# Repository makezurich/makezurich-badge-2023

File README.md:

## #MakeZurich 2023 Badge

## Pinout

## PSU
* Adafruit Feather LiPo circuit

## IO
* LoRa E5
* Shitty Addon
* Cover connectors 
* Grove connectors

## Resources

### CircuitPython
https://github.com/makezurich/badge2023-circuitpython

https://github.com/todbot/circuitpython-tricks

https://www.circuitpython.org

### LoRa E5
https://wiki.seeedstudio.com/Grove_LoRa_E5_New_Version/

https://www.hackster.io/sidikalamini/grove-lora-e5-p2p-communication-using-circuitpython-f970e6

https://files.seeedstudio.com/products/317990687/res/LoRa-E5%20AT%20Command%20Specification_V1.0%20.pdf

#### Version
| title | date | author | id | mainfont | toc | toc-depth |
| --- | --- | --- | --- | --- | --- | --- |
|"Badge"|2022-09-20|Tillo|20220920183855|Cochin|true|2|
|"Badge"|2023-04-24|Fede|?|Cochin|true|2|
|"Badge"|2023-05-12|Fede|?|Cochin|true|2|

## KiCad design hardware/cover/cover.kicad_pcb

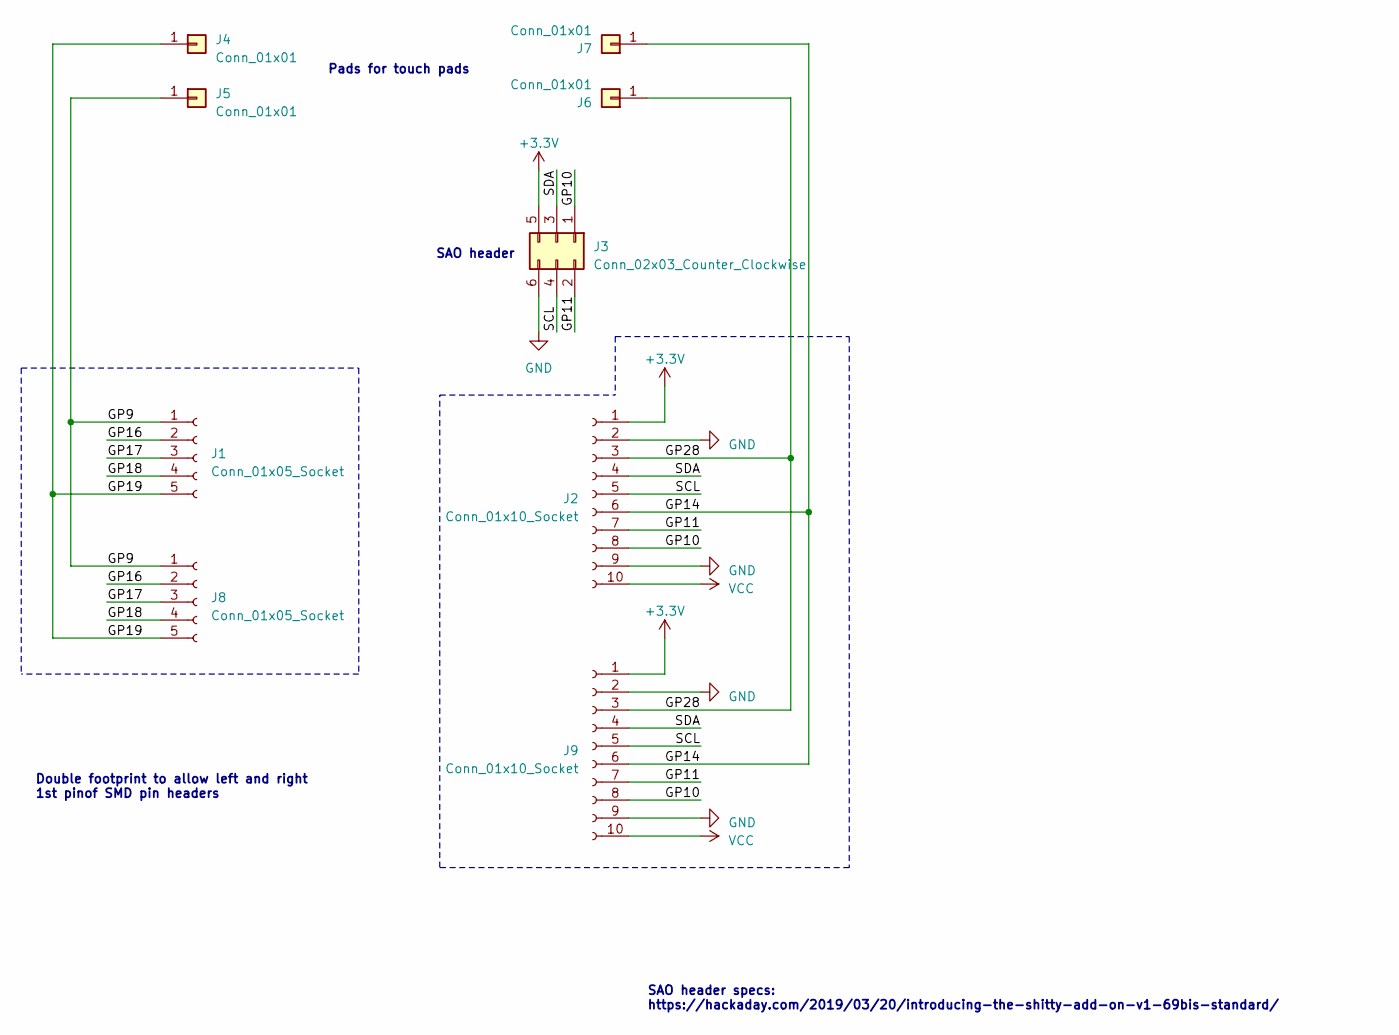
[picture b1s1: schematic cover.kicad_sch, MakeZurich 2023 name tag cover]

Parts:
J1: Conn_01x05_Socket; PinHeader_1x05_P2.54mm_Vertical_SMD_Pin1Right
J2: Conn_01x10_Socket; PinHeader_1x10_P2.54mm_Vertical_SMD_Pin1Left
J3: Conn_02x03_Counter_Clockwise; IDC-Header_2x03_P2.54mm_Vertical
J4, J5, J6, J7: Conn_01x01; SolderWirePad_1x01_SMD_1x2mm
J8: Conn_01x05_Socket; PinHeader_1x05_P2.54mm_Vertical_SMD_Pin1Left
J9: Conn_01x10_Socket; PinHeader_1x10_P2.54mm_Vertical_SMD_Pin1Right

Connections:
+3.3V: J2.1, J3.5, J9.1
/GP9: J1.1, J5.1, J8.1
/GP10: J2.8, J3.1, J9.8
/GP11: J2.7, J3.2, J9.7
/GP14: J2.6, J7.1, J9.6
/GP16: J1.2, J8.2
/GP17: J1.3, J8.3
/GP18: J1.4, J8.4
/GP19: J1.5, J4.1, J8.5
/GP28: J2.3, J6.1, J9.3
/SCL: J2.5, J3.4, J9.5
/SDA: J2.4, J3.3, J9.4
GND: J2.2, J2.9, J3.6, J9.2, J9.9
VCC: J2.10, J9.10

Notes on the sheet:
Double footprint to allow left and right 1st pinof SMD pin headers
SAO header
SAO header specs: https://hackaday.com/2019/03/20/introducing-the-shitty-add-on-v1-69bis-standard/
Pads for touch pads

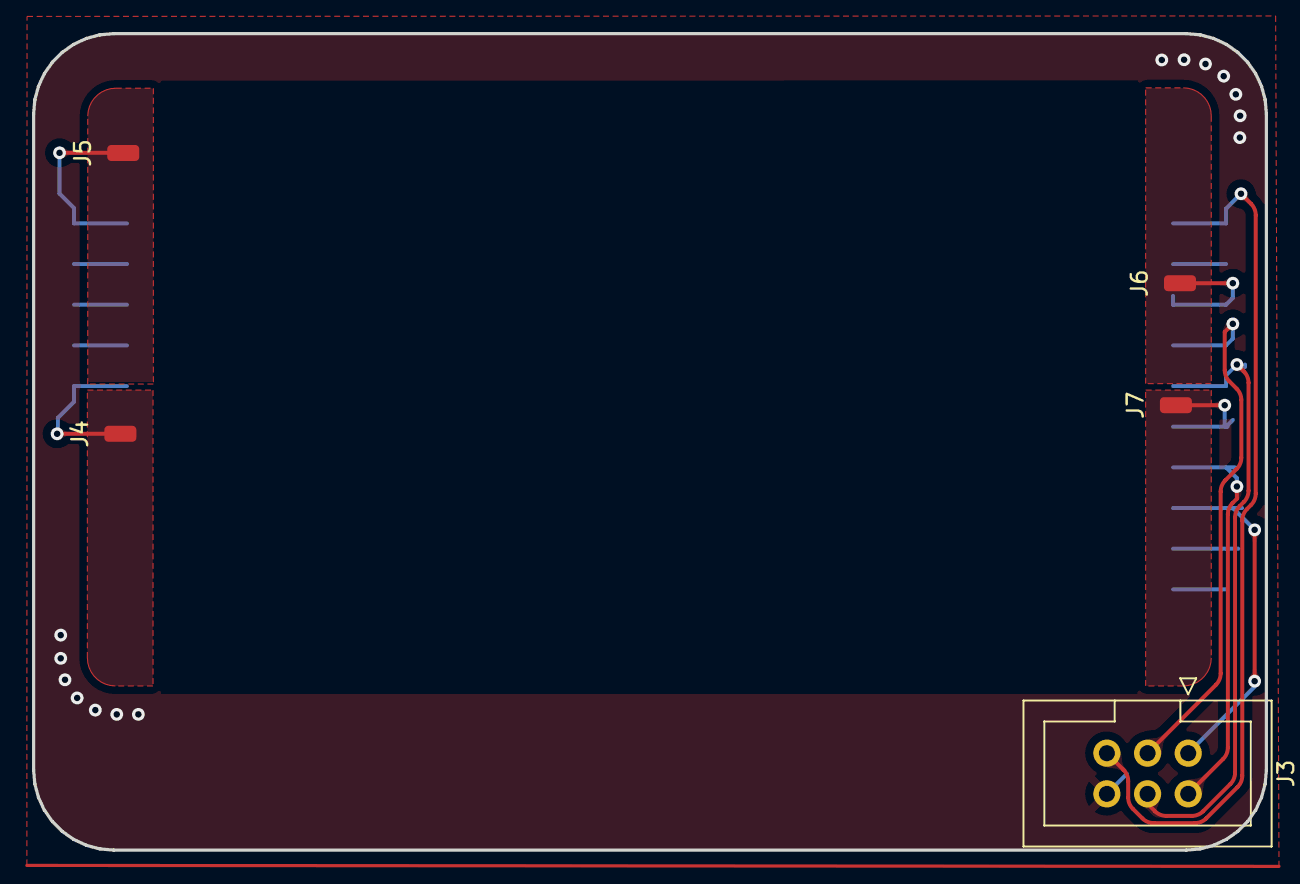
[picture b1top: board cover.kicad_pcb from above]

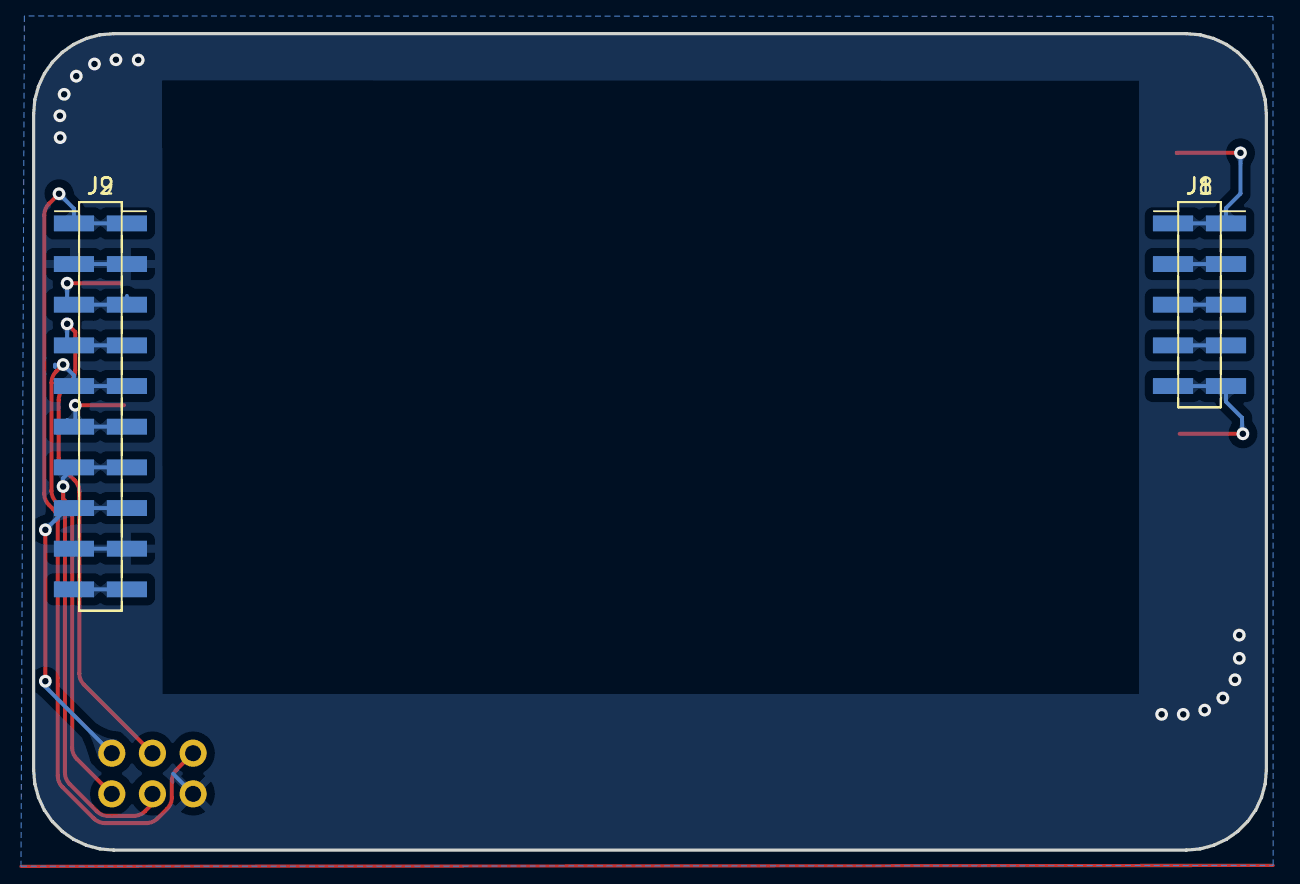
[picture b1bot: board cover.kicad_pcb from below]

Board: 2 copper layers, 77.0 x 51.0 mm, 9 parts (4 on the bottom side), 14 nets.

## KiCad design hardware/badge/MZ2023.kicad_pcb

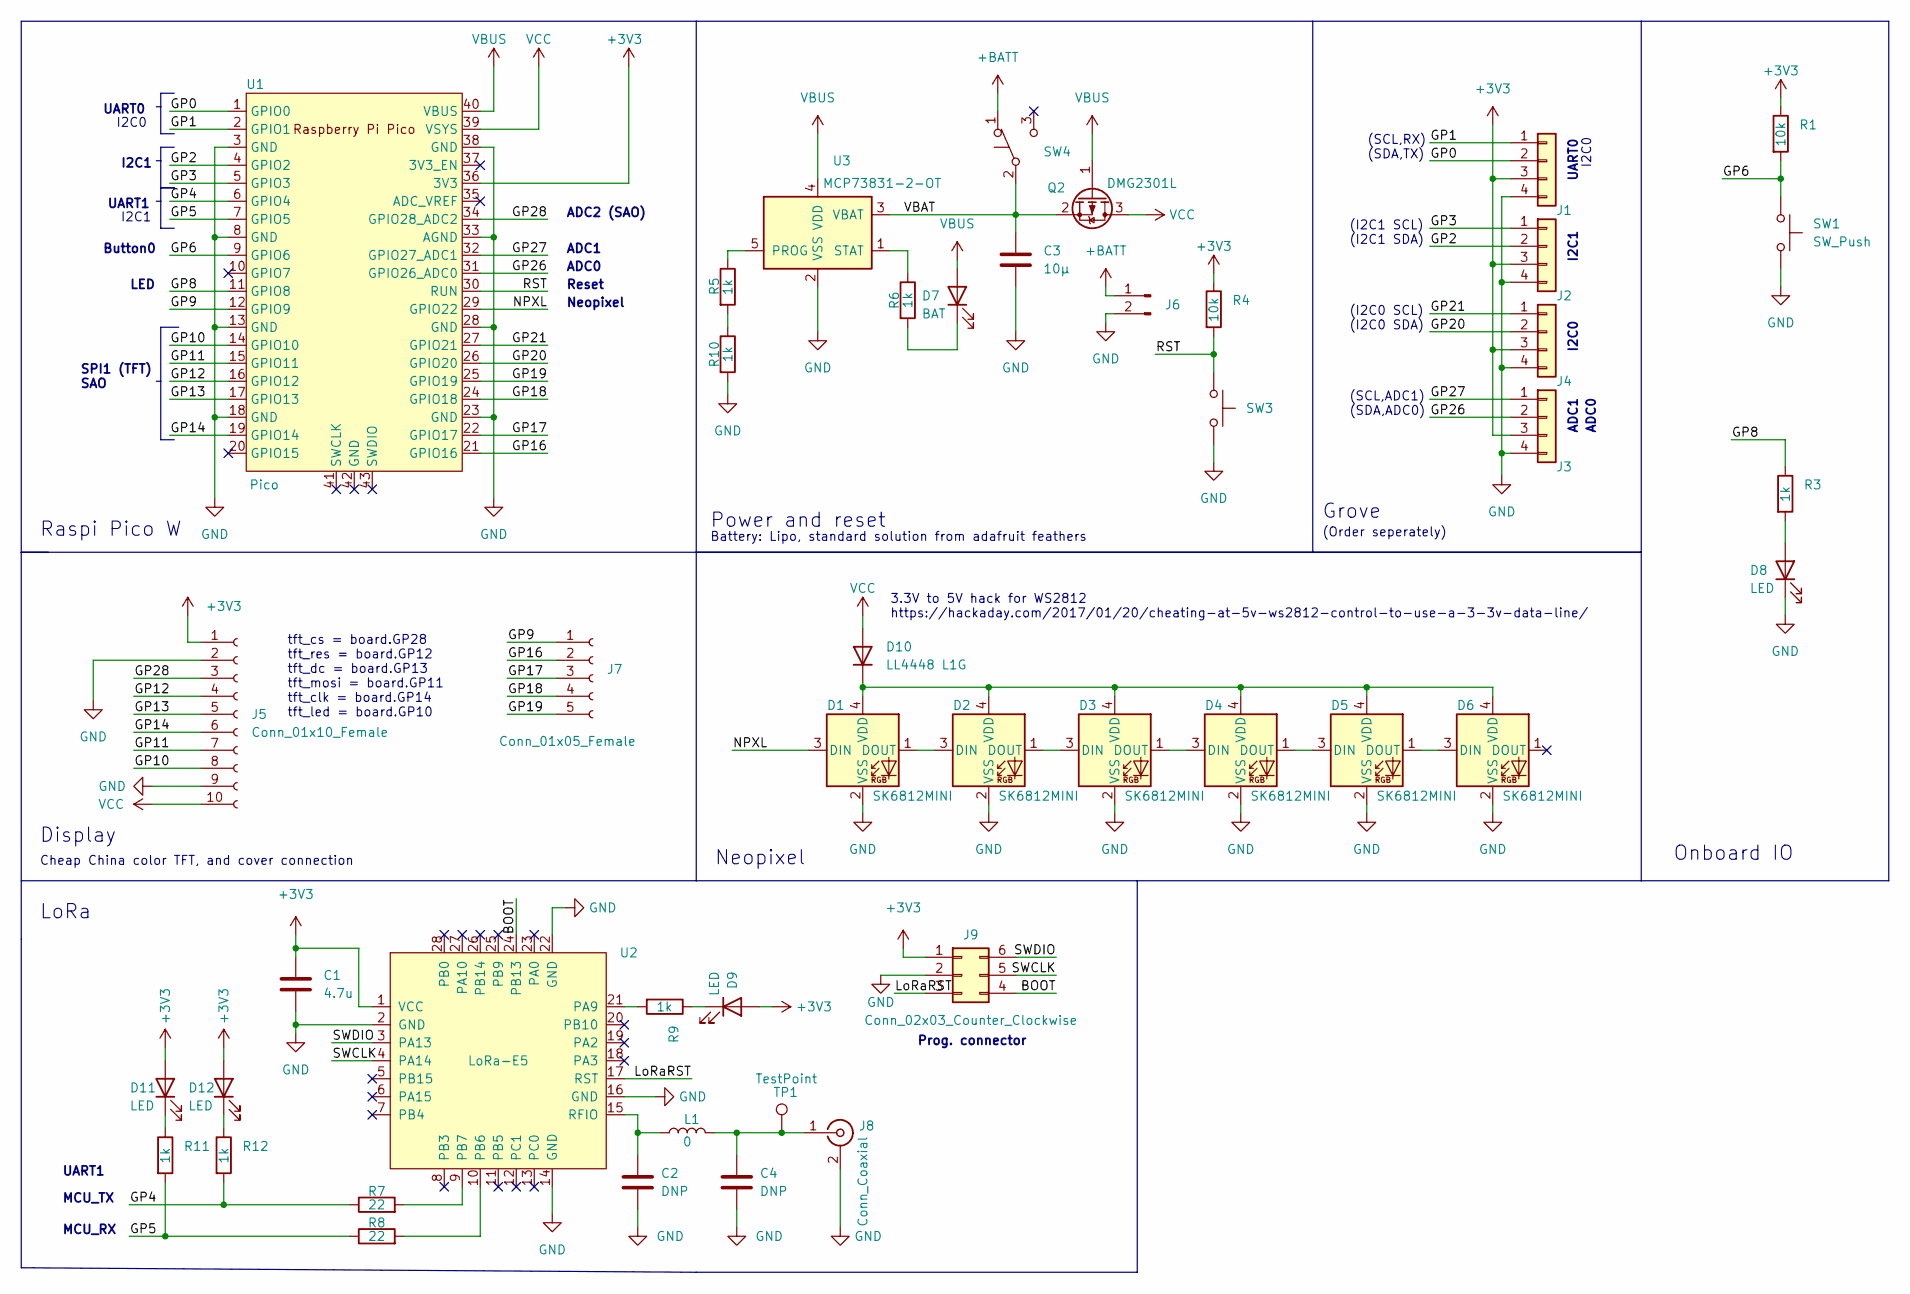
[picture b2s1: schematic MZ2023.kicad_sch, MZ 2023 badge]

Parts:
C1: 4.7u; C_0805_2012Metric; Mouser 187-CL21A475KPFNNNG
C2, C4: DNP; C_0603_1608Metric
C3: 10µ; C_1206_3216Metric_Pad1.33x1.80mm_HandSolder; Mouser 187-CL31A106MAHNNNE
D1, D2, D3, D4, D5, D6: SK6812MINI; LED_SK6812MINI_PLCC4_3.5x3.5mm_P1.75mm; Mouser 485-2659
D7: BAT; LED_0603_1608Metric_Pad1.05x0.95mm_HandSolder; Mouser 710-150060VS75000
D8, D9, D11, D12: LED; LED_0603_1608Metric_Pad1.05x0.95mm_HandSolder; Mouser 710-150060VS75000
D10: LL4448 L1G; D_MiniMELF; Digikey LL4448L1GCT-ND
J1, J2, J3, J4: Conn_01x04; Grove_SMD
J5: Conn_01x10_Female; PinHeader_1x10_P2.54mm_Vertical; Mouser 649-1012937891001BLF
J6: Conn_01x02_Male; JST_PH_S2B-PH-K_1x02_P2.00mm_Horizontal; Digikey 455-1719-ND
J7: Conn_01x05_Female; PinHeader_1x05_P2.54mm_Vertical; Mouser 649-1012937890503BLF
J8: Conn_Coaxial; U.FL_Hirose_U.FL-R-SMT-1_Vertical
J9: Conn_02x03_Counter_Clockwise; PinHeader_2x03_P2.54mm_Vertical_SMD
L1: 0; L_0805_2012Metric_Pad1.15x1.40mm_HandSolder; Mouser 603-RC0805FR-070RL
Q2: DMG2301L; SOT-23; Mouser 621-DMG2301L-7
R1, R4: 10k; R_0603_1608Metric; Mouser 603-RT0603FRE1310KL
R3, R5, R6, R9, R10, R11, R12: 1k; R_0603_1608Metric; Mouser 603-RT0603DRE071KL
R7, R8: 22; R_0603_1608Metric; Mouser 603-RT0603FRE0722RL
SW1, SW3: SW_Push; SW_Push_1P1T_NO_CK_KMR2; Digikey CKN10244CT-ND
SW4: SW_Push_SPDT; SW_CuK_OS102011MA1QN1_SPDT_Angled; Mouser 611-OS102011MA1QN1
TP1: TestPoint; PinHeader_1x01_P2.54mm_Vertical
U1: Pico; RPi_Pico_SMD_TH
U2: LoRa-E5
U3: MCP73831-2-OT; SOT-23-5; Mouser 579-MCP73831T-2ACIOT

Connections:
+3V3: C1.1, D9.2 (A), D11.2 (A), D12.2 (A), J1.3, J2.3, J3.3, J4.3, J5.1, J9.1, R1.1, R4.1, U1.36 (3V3), U2.1 (VCC)
+BATT: J6.1, SW4.1 (A)
/BOOT: J9.4, U2.24 (PB13~)
/GP0: J1.2, U1.1 (GPIO0)
/GP1: J1.1, U1.2 (GPIO1)
/GP2: J2.2, U1.4 (GPIO2)
/GP3: J2.1, U1.5 (GPIO3)
/GP4: R7.1, R12.2, U1.6 (GPIO4)
/GP5: R8.1, R11.2, U1.7 (GPIO5)
/GP6: R1.2, SW1.1, U1.9 (GPIO6)
/GP8: R3.1, U1.11 (GPIO8)
/GP9: J7.1, U1.12 (GPIO9)
/GP10: J5.8, U1.14 (GPIO10)
/GP11: J5.7, U1.15 (GPIO11)
/GP12: J5.4, U1.16 (GPIO12)
/GP13: J5.5, U1.17 (GPIO13)
/GP14: J5.6, U1.19 (GPIO14)
/GP16: J7.2, U1.21 (GPIO16)
/GP17: J7.3, U1.22 (GPIO17)
/GP18: J7.4, U1.24 (GPIO18)
/GP19: J7.5, U1.25 (GPIO19)
/GP20: J4.2, U1.26 (GPIO20)
/GP21: J4.1, U1.27 (GPIO21)
/GP26: J3.2, U1.31 (GPIO26_ADC0)
/GP27: J3.1, U1.32 (GPIO27_ADC1)
/GP28: J5.3, U1.34 (GPIO28_ADC2)
/LoRaRST: J9.3, U2.17 (RST)
/NPXL: D1.3 (DIN), U1.29 (GPIO22)
/RST: R4.2, SW3.1, U1.30 (RUN)
/SWCLK: J9.5, U2.4 (PA14)
/SWDIO: J9.6, U2.3 (PA13)
/VBAT: C3.1, Q2.2 (S), SW4.2 (B), U3.3 (VBAT)
GND: C1.2, C2.2, C3.2, C4.2, D1.2 (VSS), D2.2 (VSS), D3.2 (VSS), D4.2 (VSS), D5.2 (VSS), D6.2 (VSS), D8.1 (K), J1.4, J2.4, J3.4, J4.4, J5.2, J5.9, J6.2, J8.2 (Ext), J9.2, R10.2, SW1.2, SW3.2, U1.3 (GND), U1.8 (GND), U1.13 (GND), U1.18 (GND), U1.23 (GND), U1.28 (GND), U1.33 (AGND), U1.38 (GND), U2.2 (GND), U2.14 (GND), U2.16 (GND), U2.22 (GND), U3.2 (VSS)
unnamed: D1.1 (DOUT), D2.3 (DIN)
unnamed: D1.4 (VDD), D2.4 (VDD), D3.4 (VDD), D4.4 (VDD), D5.4 (VDD), D6.4 (VDD), D10.1 (K)
unnamed: D2.1 (DOUT), D3.3 (DIN)
unnamed: D3.1 (DOUT), D4.3 (DIN)
unnamed: D4.1 (DOUT), D5.3 (DIN)
unnamed: D5.1 (DOUT), D6.3 (DIN)
unnamed: D7.1 (K), R6.2
unnamed: D8.2 (A), R3.2
unnamed: D9.1 (K), R9.1
unnamed: D11.1 (K), R11.1
unnamed: D12.1 (K), R12.1
unnamed: C4.1, J8.1 (In), L1.2, TP1.1
unnamed: R5.2, R10.1
unnamed: R9.2, U2.21 (PA9)
unnamed: R8.2, U2.10 (PB6)
unnamed: R7.2, U2.9 (PB7)
unnamed: C2.1, L1.1, U2.15 (RFIO)
unnamed: R5.1, U3.5 (PROG)
unnamed: R6.1, U3.1 (STAT)
VBUS: D7.2 (A), Q2.1 (G), U1.40 (VBUS), U3.4 (VDD)
VCC: D10.2 (A), J5.10, Q2.3 (D), U1.39 (VSYS)

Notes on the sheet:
Power and reset
(I2C1 SCL) (I2C1 SDA)
Prog. connector
(SCL,RX) (SDA,TX)
I2C0
Cheap China color TFT, and cover connection
ADC1
Raspi Pico W
ADC2 (SAO)
ADC0
I2C1
Button0
(SCL,ADC1) (SDA,ADC0)
(Order seperately)
UART0
Reset
UART1
Neopixel
tft_cs = board.GP28 tft_res = board.GP12 tft_dc = board.GP13 tft_mosi = board.GP11 tft_clk = board.GP14 tft_led = board.GP10
(I2C0 SCL) (I2C0 SDA)
MCU_TX
3.3V to 5V hack for WS2812 https://hackaday.com/2017/01/20/cheating-at-5v-ws2812-control-to-use-a-3-3v-data-line/
MCU_RX
LoRa
Onboard IO
Display
Neopixel
Battery: Lipo, standard solution from adafruit feathers
LED
Grove
SPI1 (TFT) SAO

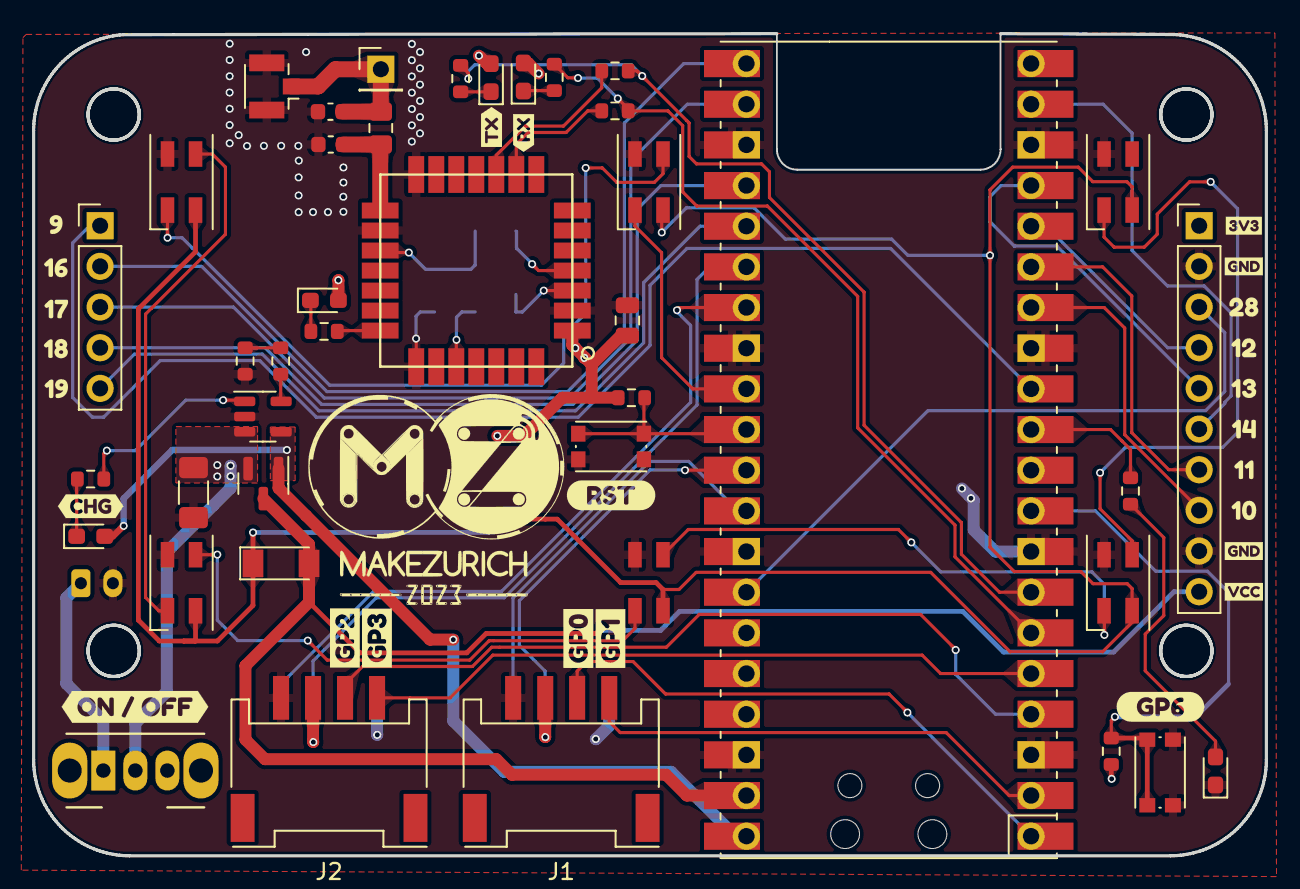
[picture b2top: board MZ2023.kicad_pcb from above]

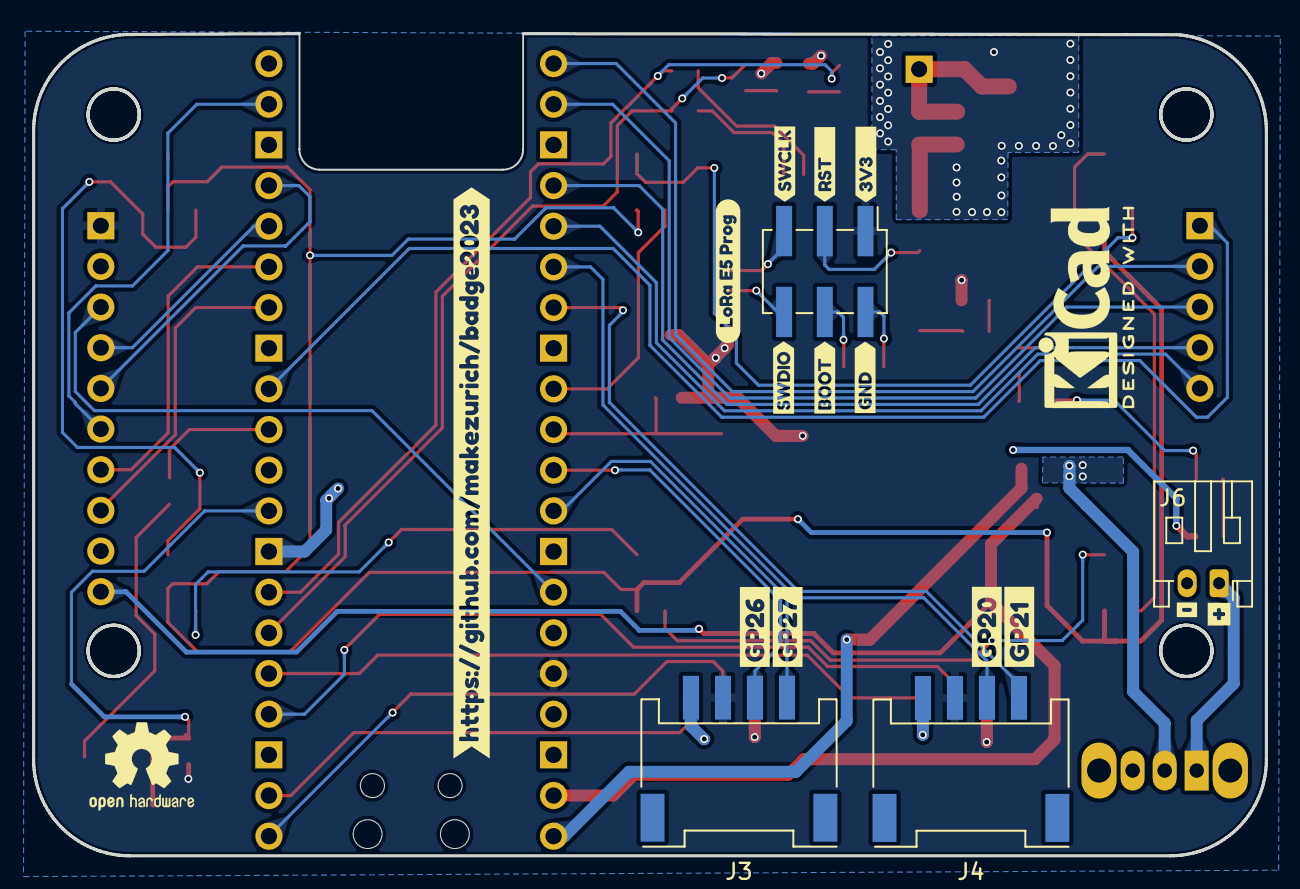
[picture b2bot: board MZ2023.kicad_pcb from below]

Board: 2 copper layers, 77.0 x 51.4 mm, 84 parts (18 on the bottom side), 54 nets.

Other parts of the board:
kibuzzard-637FABC0: G***; kibuzzard-637FABC0
kibuzzard-637FABEE: G***; kibuzzard-637FABEE
kibuzzard-637FABF7: G***; kibuzzard-637FABF7
kibuzzard-637FAC0A: G***; kibuzzard-637FAC0A
kibuzzard-637FAC01: G***; kibuzzard-637FAC01
kibuzzard-6368F4A2: G***; kibuzzard-6368F4A2
kibuzzard-6368F4DE: G***; kibuzzard-6368F4DE
kibuzzard-6368F4F7: G***; kibuzzard-6368F4F7
kibuzzard-6368F490: G***; kibuzzard-6368F490
kibuzzard-6368F495: G***; kibuzzard-6368F495
kibuzzard-6368F503: G***; kibuzzard-6368F503
kibuzzard-6368F610: G***; kibuzzard-6368F610
kibuzzard-6370DC90: G***; kibuzzard-6370DC90
kibuzzard-6370DC98: G***; kibuzzard-6370DC98
kibuzzard-6370DCA7: G***; kibuzzard-6370DCA7
kibuzzard-6372B00C: G***; kibuzzard-6372B00C
kibuzzard-6445C3D4: G***; kibuzzard-6445C3D4
kibuzzard-6445C3F3: G***; kibuzzard-6445C3F3
kibuzzard-6445C7AF: G***; kibuzzard-6445C7AF
kibuzzard-6445C7B7: G***; kibuzzard-6445C7B7
kibuzzard-6445C7DF: G***; kibuzzard-6445C7DF
kibuzzard-6445C7E9: G***; kibuzzard-6445C7E9
kibuzzard-6445C08E: G***; kibuzzard-6445C08E
kibuzzard-6445C19F: G***; kibuzzard-6445C19F
kibuzzard-6445C37B, kibuzzard-6445C37B#2: G***; kibuzzard-6445C37B
kibuzzard-6464F9A8: G***; kibuzzard-6464F9A8
kibuzzard-6464F92F: G***; kibuzzard-6464F92F
kibuzzard-6464F984: G***; kibuzzard-6464F984
kibuzzard-64568B8C: G***; kibuzzard-64568B8C
kibuzzard-64568C60: G***; kibuzzard-64568C60
kibuzzard-64568EFC: G***; kibuzzard-64568EFC
kibuzzard-64568F15: G***; kibuzzard-64568F15
kibuzzard-636923C0: G***; kibuzzard-636923C0
kibuzzard-6369234D: G***; kibuzzard-6369234D
kibuzzard-6461287C: G***; kibuzzard-6461287C
kibuzzard-63692365: G***; kibuzzard-63692365
kibuzzard-64457602: G***; kibuzzard-64457602
kibuzzard-64484314: G***; kibuzzard-64484314

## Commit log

2022-11-08 gitignore
2022-11-08 PCB Layout
2023-01-11 prototype
2023-03-23 some parts anotated
2023-04-24 new version: * added Seeed Studio LoRa e5 module * changed WS2812 LED from 5x5mm to 3.5x3.5mm footprint * changed WS2812 LED positions. From circle to "rectangular" with intention of becoming the top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
2023-05-12 lora e5 v0.2 * changed grove connectors to right angle version * changed footprint for RDB LEDs WS2812B -> SK6812MINI (compatible with NeoPixels * mechanical switch (SW4) now cut the BAT+ instead of 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
2023-05-13 added GND under antenna, added teardrops
2023-05-14 improvements to the LoRa antenna * changed the shape of the copper plane underneath the LoRa antenna path * moved D1-DOUT track on btm outside the antenna btm gnd plane
2023-05-14 changing silk: lipo charge LED -> CHG
2023-05-15 adding component Mouser/Digikey part numbers to schematic. Generating ibom
2023-05-15 parts numbers: completing digikey
2023-06-02 Add pinout.
2023-06-02 Update.
2023-06-03 badge: improving bottomo slick
2023-06-03 updating make zurich logo size
2023-06-03 cover: adding nametag cover
2023-06-03 badge: updating PDF layout
2023-06-03 cover: adding PDFs schematic & layout
2023-06-03 removing unused PDF exports of individual layout layers
